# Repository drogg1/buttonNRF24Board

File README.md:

# buttonNRF24Board
An nrf24L01+ board inside a large button as this makes it accessible for those who have poor motion control.

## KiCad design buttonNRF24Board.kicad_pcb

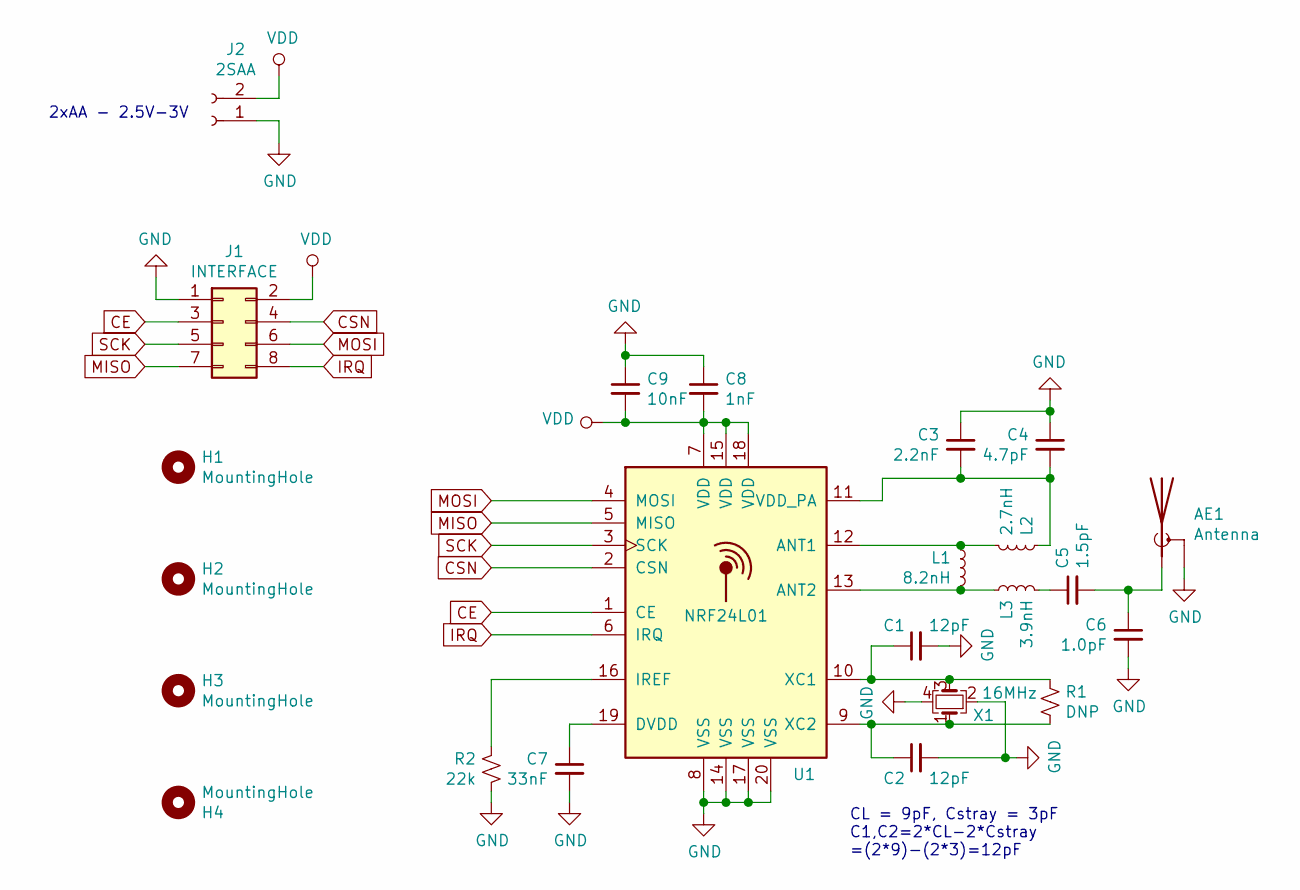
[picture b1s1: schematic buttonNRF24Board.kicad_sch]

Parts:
AE1: Antenna; Texas_SWRA117D_2.4GHz_Left
C1, C2: 12pF; C_0402_1005Metric
C3: 2.2nF; C_0402_1005Metric
C4: 4.7pF; C_0402_1005Metric
C5: 1.5pF; C_0402_1005Metric
C6: 1.0pF; C_0402_1005Metric
C7: 33nF; C_0402_1005Metric
C8: 1nF; C_0402_1005Metric
C9: 10nF; C_0402_1005Metric
H1, H3: MountingHole; hole2.2
H2, H4: MountingHole; hole1.8
J1: INTERFACE; PinHeader_2x04_P2.54mm_Vertical
J2: 2SAA; PinHeader_1x02_P2.54mm_Vertical
L1: 8.2nH; L_0402_1005Metric
L2: 2.7nH; L_0402_1005Metric
L3: 3.9nH; L_0402_1005Metric
R1: DNP; R_0402_1005Metric
R2: 22k; R_0402_1005Metric
U1: NRF24L01; QFN-20-1EP_4x4mm_P0.5mm_EP2.5x2.5mm
X1: 16MHz; Crystal_SMD_3225-4Pin_3.2x2.5mm

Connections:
CE: J1.3, U1.1 (CE)
CSN: J1.4, U1.2 (CSN)
EP: AE1.2 (Shield), C1.2, C2.2, C3.1, C4.1, C6.2, C7.2, C8.1, C9.1, J1.1, J2.1, R2.1, U1.8 (VSS), U1.14 (VSS), U1.17 (VSS), U1.20 (VSS), U1.21 (EP), X1.2, X1.4
IRQ: J1.8, U1.6 (IRQ)
MISO: J1.7, U1.5 (MISO)
MOSI: J1.6, U1.4 (MOSI)
unnamed: AE1.1 (A), C5.2, C6.1
unnamed: C1.1, R1.2, U1.10 (XC1), X1.3
unnamed: C2.1, R1.1, U1.9 (XC2), X1.1
unnamed: C3.2, C4.2, L2.2, U1.11 (VDD_PA)
unnamed: C5.1, L3.1
unnamed: C7.1, U1.19 (DVDD)
unnamed: L1.1, L3.2, U1.13 (ANT2)
unnamed: L1.2, L2.1, U1.12 (ANT1)
unnamed: R2.2, U1.16 (IREF)
SCK: J1.5, U1.3 (SCK)
VDD: C8.2, C9.2, J1.2, J2.2, U1.7 (VDD), U1.15 (VDD), U1.18 (VDD)

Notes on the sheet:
2xAA - 2.5V-3V
CL = 9pF, Cstray = 3pF C1,C2=2*CL-2*Cstray =(2*9)-(2*3)=12pF

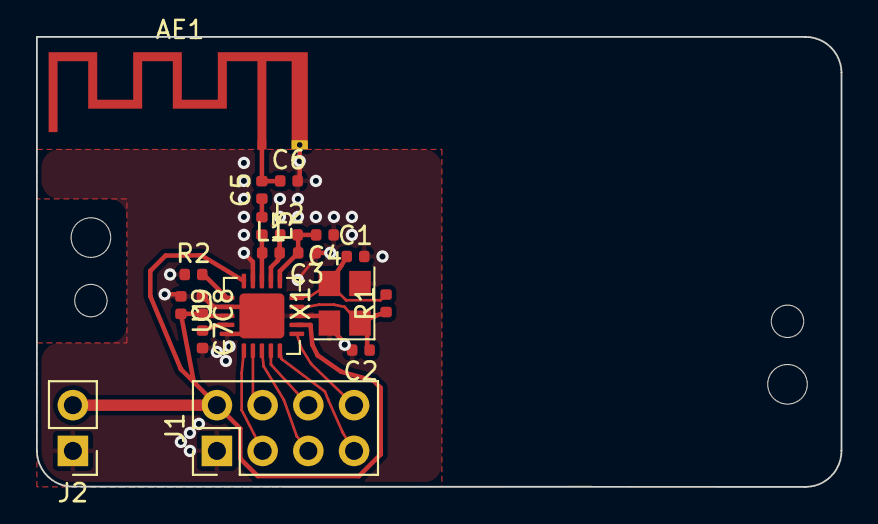
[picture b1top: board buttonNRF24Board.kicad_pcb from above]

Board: 2 copper layers, 44.7 x 25.0 mm, 23 parts (0 on the bottom side), 17 nets.

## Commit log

2021-01-21 Initial commit of large button nrf24L01+ board for accessible use.
2021-01-22 Tweaking board shape and traces
